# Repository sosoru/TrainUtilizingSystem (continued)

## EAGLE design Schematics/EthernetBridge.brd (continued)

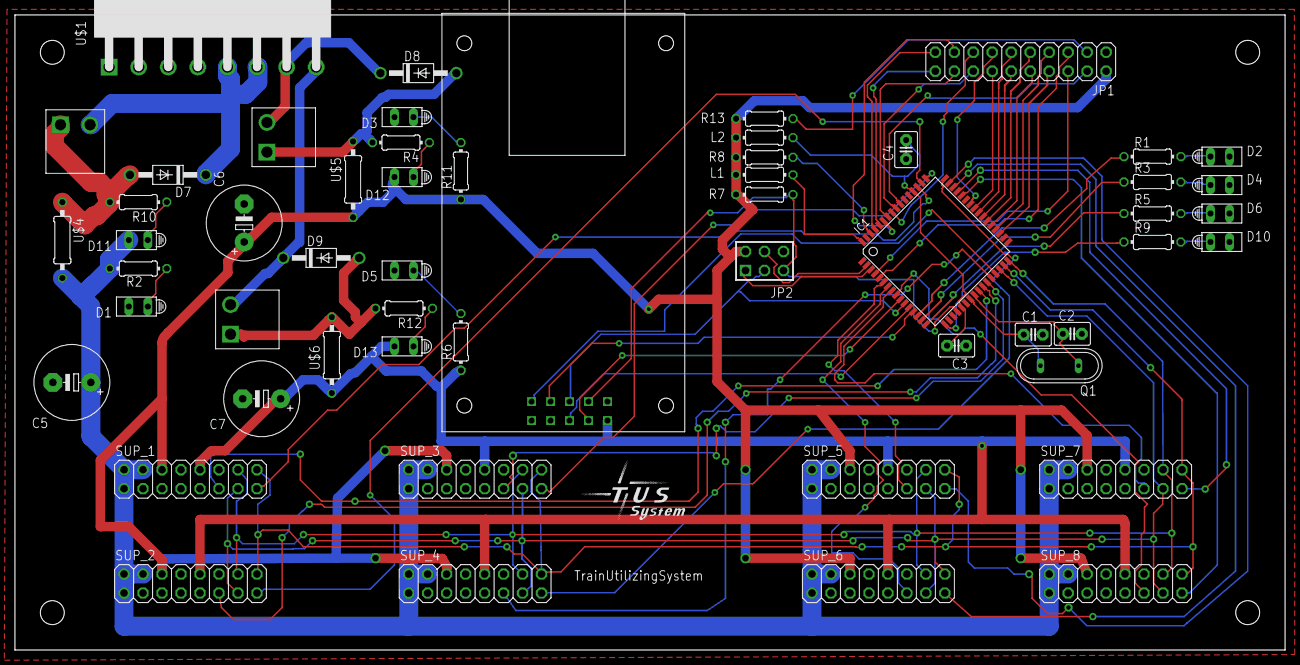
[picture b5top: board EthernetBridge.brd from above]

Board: 2 copper layers, 170.0 x 85.0 mm, 55 parts (0 on the bottom side), 74 nets.

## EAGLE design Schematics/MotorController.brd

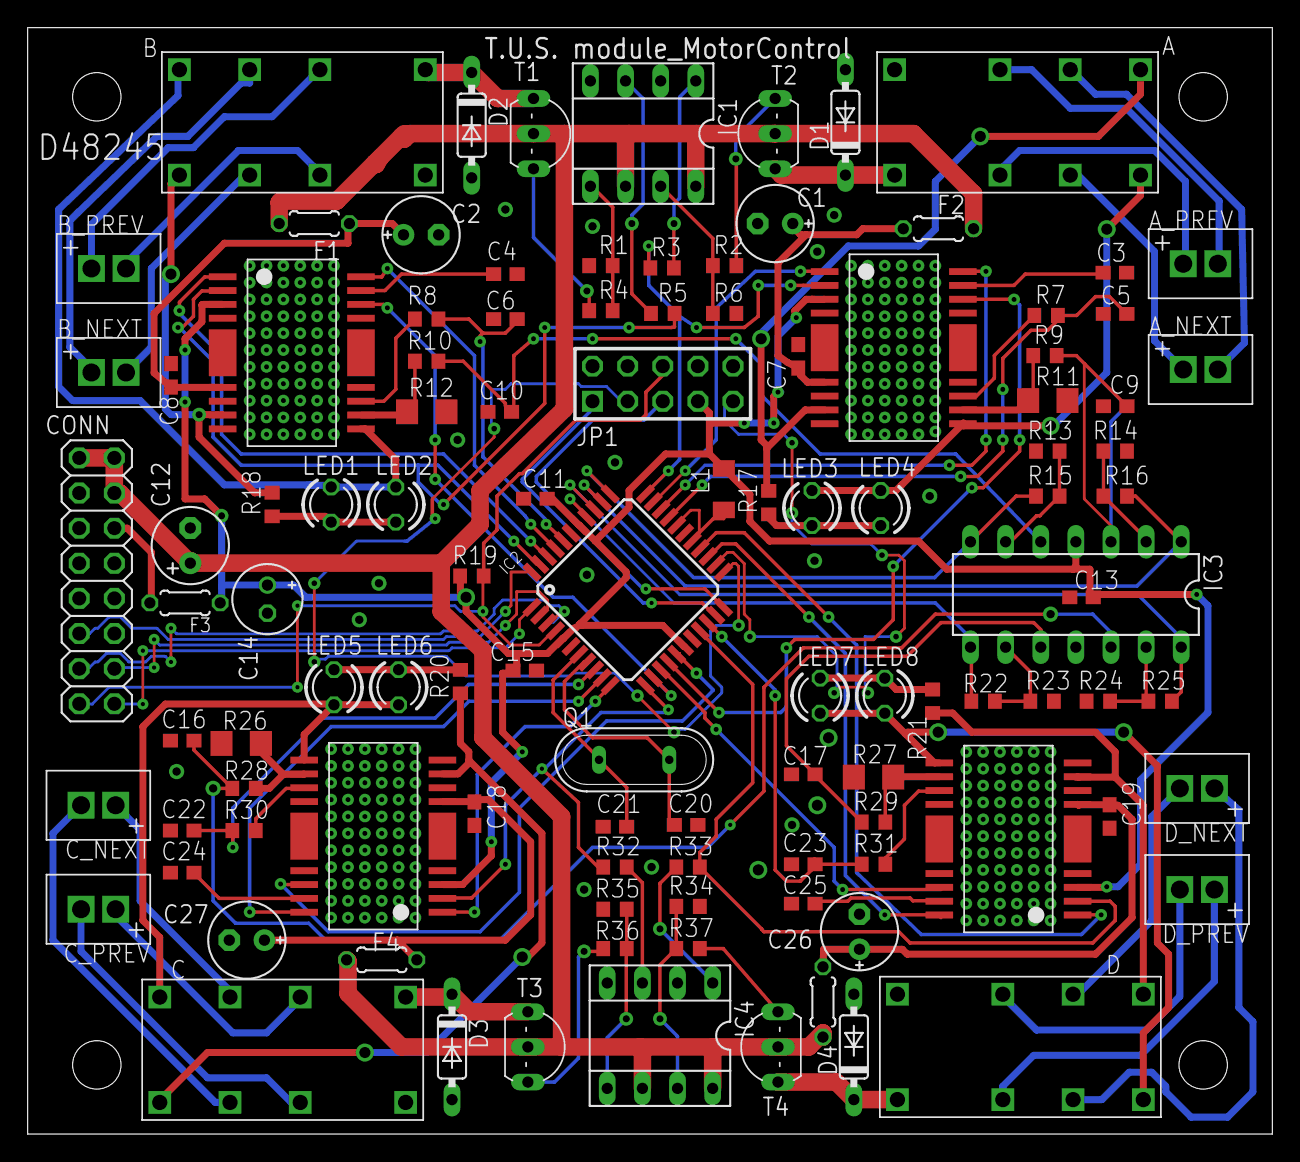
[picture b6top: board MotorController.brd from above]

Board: 2 copper layers, 90.0 x 80.0 mm, 109 parts (0 on the bottom side), 108 nets.

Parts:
A: 942H; 941H-2C-12D
A_NEXT: XH-2
A_PREV: XH-2
B: 942H; 941H-2C-12D
B_NEXT: XH-2
B_PREV: XH-2
C: 942H; 941H-2C-12D
C1, C2, C26, C27: E2,5-6E
C3, C4, C7, C8, C11, C13, C15, C18, C19, C24, C25: 0.1u; C0603
C5, C6, C22, C23: 4.7u; C0603
C9, C10, C16, C17: 0.47u; C0603
C12: 100u; E2,5-6
C14: 100u; E2-5
C20, C21: 22p; C0603
CONN: TUS_MODULE_SUPPLY; 2X08
C_NEXT: XH-2
C_PREV: XH-2
D: 942H; 941H-2C-12D
D1, D2, D3, D4: 1N4148DO35-7; DO35-7
D_NEXT: XH-2
D_PREV: XH-2
F1, F2, F3, F4, F5: POLYSWITCH_20204/5; 0204/5
IC1, IC4: TLP621-2; SOCKET-08
IC2: MEGA164P/324P/644P-AU; TQFP44
IC3: OPA4234P; DIL14
JP1: AVR-JTAG-10
L1: 47u; L3216C
LED1, LED3, LED5, LED7: G; LED3MM
LED2, LED4, LED6, LED8: O; LED3MM
Q1: 20.000M; QS
R1, R6, R34, R35: 100k; R0603
R2, R4, R19, R36, R37: 10k; R0603
R3, R5, R32, R33: 500; R0603
R7, R8, R17, R18, R20, R21, R30, R31: 3.3k; R0603
R9, R10, R28, R29: 33k; R0603
R11, R12, R26, R27: 0.01; R1206
R13, R14, R23, R24: 100; R0603
R15, R16, R22, R25: 25k; R0603
T1, T2, T3, T4: 2SC1815; TO92-ECB
U$1, U$2, U$3, U$4: TB6559; HSOP-16

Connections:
!RESET: CONN.15, IC2.4, JP1.6, R19.2
!SS: CONN.11, IC2.44
+5V: C11.2, C13.2, C14.+, C15.2, F3.2, IC2.5, IC2.17, IC2.38, IC3.4, JP1.7, L1.1, R19.1, U$1.3, U$2.3, U$3.3, U$4.3
+12V: C12.+, CONN.1, CONN.2, CONN.4, F1.2, F2.2, F4.2, F5.2, IC1.6, IC1.8, IC4.6, IC4.8, T1.C, T2.C, T3.C, T4.C
A_OUT1: A.8, R17.2, U$1.7
A_OUT2: A.9, LED3.A, LED4.K, U$1.9
A_OUT3: C.8, R20.2, U$3.7
A_OUT4: C.9, LED5.A, LED6.K, U$3.9
A_OUT5: B.8, R18.2, U$2.7
A_OUT6: B.9, LED1.A, LED2.K, U$2.9
A_OUT7: D.8, R21.2, U$4.7
A_OUT8: D.9, LED7.A, LED8.K, U$4.9
CTRL_A_1: IC2.32, U$1.1
CTRL_A_2: IC2.31, U$1.16
CTRL_A_3: IC2.33, R3.1, U$1.2
CTRL_A_ALERT: C5.1, IC2.30, R7.2
CTRL_A_PWM: IC2.15, U$1.14
CTRL_B_1: IC2.42, U$2.1
CTRL_B_2: IC2.41, U$2.16
CTRL_B_3: IC2.43, R5.1, U$2.2
CTRL_B_ALERT: C6.1, IC2.40, R8.2
CTRL_B_PWM: IC2.13, U$2.14
CTRL_C_1: IC2.11, U$3.1
CTRL_C_2: IC2.10, U$3.16
CTRL_C_3: IC2.12, R32.1, U$3.2
CTRL_C_ALERT: C22.1, IC2.9, R30.2
CTRL_C_PWM: IC2.16, U$3.14
CTRL_D_1: IC2.26, U$4.1
CTRL_D_2: IC2.25, U$4.16
CTRL_D_3: IC2.19, R33.1, U$4.2
CTRL_D_ALERT: C23.1, IC2.20, R31.2
CTRL_D_PWM: IC2.14, U$4.14
D: D.4, D_PREV.P$2
FEEDBACK_A: IC2.35, IC3.1, R16.2
FEEDBACK_B: IC2.34, IC3.7, R15.2
FEEDBACK_C: IC2.36, IC3.14, R25.2
FEEDBACK_D: IC2.37, IC3.8, R22.2
GND: A.1, B.1, C.1, C1.-, C2.-, C3.2, C4.2, C5.2, C6.2, C7.1, C8.1, C9.2, C10.2, C11.1, C12.-, C13.1, C14.-, C15.1, C16.2, C17.2, C18.1, C19.1, C20.1, C21.1, C22.2, C23.2, C24.2, C25.2, C26.-, C27.-, CONN.3, CONN.5, CONN.7, CONN.8, CONN.9, CONN.12, D.1, D1.A, D2.A, D3.A, D4.A, IC1.2, IC1.4, IC2.6, IC2.18, IC2.28, IC2.39, IC3.11, IC4.2, IC4.4, JP1.2, JP1.10, R1.2, R6.2, R11.2, R12.2, R13.2, R14.2, R23.2, R24.2, R26.2, R27.2, R34.2, R35.2, U$1.4, U$1.8, U$1.12, U$1.13, U$1.FIN_1, U$1.FIN_2, U$2.4, U$2.8, U$2.12, U$2.13, U$2.FIN_1, U$2.FIN_2, U$3.4, U$3.8, U$3.12, U$3.13, U$3.FIN_1, U$3.FIN_2, U$4.4, U$4.8, U$4.12, U$4.13, U$4.FIN_1, U$4.FIN_2
MISO: CONN.14, IC2.2
MOSI: CONN.16, IC2.1
unnamed: IC2.27, IC2.29, L1.2
unnamed: C21.2, IC2.7, Q1.1
unnamed: C20.2, IC2.8, Q1.2
unnamed: R7.1, U$1.11
unnamed: C3.1, U$1.15
unnamed: IC1.1, R3.2
unnamed: IC1.7, R2.1, R6.1
unnamed: LED3.K, LED4.A, R17.1
unnamed: C24.1, U$3.15
unnamed: C1.+, C7.2, F2.1, U$1.5
unnamed: IC3.2, R14.1, R16.1
unnamed: R30.1, U$3.11
unnamed: A.6, A_NEXT.P$2
unnamed: R9.1, R11.1, U$1.10
unnamed: A.11, A_NEXT.P$1
unnamed: A.4, A_PREV.P$2
unnamed: A.13, A_PREV.P$1
unnamed: C18.2, C27.+, F4.1, U$3.5
unnamed: LED5.K, LED6.A, R20.1
unnamed: IC1.3, R5.2
unnamed: C9.1, IC3.3, R9.2
unnamed: C.6, C_NEXT.P$2
unnamed: C.11, C_NEXT.P$1
unnamed: C.4, C_PREV.P$2
unnamed: C.13, C_PREV.P$1
unnamed: IC4.5, R35.1, R36.1
unnamed: C.16, D3.C, T3.E
unnamed: R36.2, T3.B
unnamed: IC3.13, R24.1, R25.1
unnamed: C16.1, IC3.12, R28.2
unnamed: R26.1, R28.1, U$3.10
unnamed: C4.1, U$2.15
unnamed: R8.1, U$2.11
unnamed: C2.+, C8.2, F1.1, U$2.5
unnamed: LED1.K, LED2.A, R18.1
unnamed: IC4.1, R33.2
unnamed: B.6, B_NEXT.P$2
unnamed: B.11, B_NEXT.P$1
unnamed: B.4, B_PREV.P$2
unnamed: B.13, B_PREV.P$1
unnamed: IC1.5, R1.1, R4.1
unnamed: B.16, D2.C, T1.E
unnamed: R4.2, T1.B
unnamed: IC3.6, R13.1, R15.1
unnamed: C10.1, IC3.5, R10.2
unnamed: R10.1, R12.1, U$2.10
unnamed: C25.1, U$4.15
unnamed: R31.1, U$4.11
unnamed: C19.2, C26.+, F5.1, U$4.5
unnamed: LED7.K, LED8.A, R21.1
unnamed: IC4.3, R32.2
unnamed: D.6, D_NEXT.P$2
unnamed: D.11, D_NEXT.P$1
unnamed: CONN.6, F3.1
unnamed: D.13, D_PREV.P$1
unnamed: IC4.7, R34.1, R37.1
unnamed: D.16, D4.C, T4.E
unnamed: R37.2, T4.B
unnamed: IC3.9, R22.1, R23.1
unnamed: C17.1, IC3.10, R29.2
unnamed: R27.1, R29.1, U$4.10
unnamed: A.16, D1.C, T2.E
unnamed: R2.2, T2.B
SCK: CONN.13, IC2.3
TCK: IC2.21, JP1.1
TDI: IC2.24, JP1.9
TDO: IC2.23, JP1.3
TMS: IC2.22, JP1.5
